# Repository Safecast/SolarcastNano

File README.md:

# Solarcast Nano

SCNano-1.0          Original Design files for Solarcast Nano 1.0 (PCB in Altium, Mechanical in Alibre)

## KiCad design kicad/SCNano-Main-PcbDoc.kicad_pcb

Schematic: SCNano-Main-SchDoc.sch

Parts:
ANT1: 3G Antenna
BAT1: KEYSTONE_1049
BOM1: Battery - 1of 2
BOM2: Battery - 2 of 2
C1: CAP POL RB13-25
CON1: SC_CON_GEIGIE_4PIN
IC1: SN74LV4052A
J1: (no value)
MOD1: LiPo Charger
MOD2, MOD2_2: FONA 3G
MOD3: Current Sensor
MOD4: 3-Axis
MOD5: GPS
MOD6: Nano V2
MOD7: DAPLink 1.5
MOD8: MicroUSB
OLED1: OLED 128x64
Q1, Q2, Q3, Q4: STU85N3LH5
SOLARPANEL1: VOLTAIC_SOLAR_PANEL_1W
SW1: SW-DPDT
VREG1: Regulator 3.3V
VREG2: Regulator Variable

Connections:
3V3: CON1.2 (RED(3V3)), IC1.16 (VCC), MOD2.4 (Vio), MOD2.5 (RST(Reset)), MOD3.1 (Vcc), MOD4.2 (3Vo), MOD5.8 (VIN), MOD6.2-1 (VDD(3.3V)), MOD7.2-1 (VDD/+3.3Vout), OLED1.1 (VCC), VREG1.1 (VOUT)
/BAT-BUS: MOD1.3 (B+), MOD3.5 (Vin-), VREG1.3 (VIN), VREG2.1 (VIN)
/BAT-POS: BAT1.1 (+), BAT1.3 (+), SW1.1
/BAT-SW: MOD3.6 (Vin+), SW1.2
/ENABLE-CELL: IC1.9 (B), MOD6.3-4 (P08), Q1.1 (G)
/ENABLE-GEIG: MOD6.3-1 (P03), Q3.1 (G)
/ENABLE-GPS: IC1.10 (A), MOD6.3-3 (P07), Q4.1 (G)
/ENABLE_TWI: MOD6.3-2 (P06), Q2.1 (G)
/FONA-BAT: MOD2.2 (Battery), VREG2.3 (VOUT)
/FONA-RX: IC1.2 (2Y2), MOD2.6 (RX)
/FONA-TX: IC1.15 (1Y2), MOD2.7 (TX)
/GEIGER0: CON1.4 (YEL(GEIGER0)), MOD6.1-4 (P04), MOD7.1-4 (NC[P04])
/GEIGER1: CON1.3 (WHT(GEIGER1)), MOD6.1-3 (P05), MOD7.1-3 (NC[P05])
/GND-CELL: MOD2.3 (GND), MOD2.11 (Key), Q1.2 (D), VREG2.2 (GND)
/GND-GEIG: CON1.1 (BLK(GND)), Q3.2 (D)
/GND-GPS: MOD5.7 (GND), Q4.2 (D)
/GND-TWI: MOD3.2 (Gnd), OLED1.2 (GND), Q2.2 (D)
/LIS-INT: MOD4.8 (INT), MOD6.3-5 (P21)
/MCU-RX: IC1.13 (1-COM), MOD6.2-4 (N2:RX/P30), MOD7.2-4 (DL:TXD[P30])
/MCU-SWCLK: MOD6.1-1 (DCLK), MOD7.1-1 (SWDCLK)
/MCU-SWDIO: MOD6.1-2 (DIO), MOD7.1-2 (SWDIO)
/MCU-TX: IC1.3 (2-COM), MOD6.2-3 (N2:TX/P29), MOD7.2-3 (DL:RXD[P29])
/NANO_VIN: MOD6.1-6 (VIN(USB5V)), MOD7.1-6 (VIN/USB5V)
/PANEL-POS: J1.1, MOD1.1 (DCIN+[TB1]), MOD8.5 (5V)
/TWI-SCL: MOD3.3 (Scl), MOD4.4 (SCL), MOD6.2-5 (N2:RTS/P02), MOD7.2-5 (DL:CTS[P31]), OLED1.3 (SCL)
/TWI-SDA: MOD3.4 (Sda), MOD4.5 (SDA), MOD6.2-2 (N2:CTS/P28), MOD7.2-2 (DL:RTS[P28]), OLED1.4 (SDA)
/UGPS-RX: IC1.5 (2Y1), MOD5.6 (RX)
/UGPS-TX: IC1.14 (1Y1), MOD5.5 (TX)
GND: BAT1.2 (-), BAT1.4 (-), C1.2, IC1.6 (INH), IC1.7 (GND), IC1.8 (GND), J1.2, MOD1.2 (DCIN-[TB1]), MOD1.4 (GND), MOD1.6 (C4-/GND), MOD1.8 (GND), MOD4.3 (GND), MOD6.1-5 (GND), MOD6.2-6 (GND), MOD7.1-5 (GND), MOD7.2-6 (GND), MOD8.1 (GND), Q1.3 (S), Q2.3 (S), Q3.3 (S), Q4.3 (S), VREG1.2 (GND)
unnamed: C1.1, MOD1.5 (C4+)

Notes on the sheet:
=sheetnumber
=organization
=address1
=address2
=address3
=address4
=sheettotal
=title
=documentnumber
=revision
=CurrentDate
=CurrentTime
=DocumentFullPathAndName
Title
Size:
Number:
Date:
File:
Revision:
Sheet
Time:
>>> Cable to Geiger Board
Note: USB A(F)/Micro-B(M) Retractable Cable
FET0
FET1
FET2
FET3
Note: Misc. Headers, Hardware
Note: Enclosure: Pelican 1040, modified with circular cutout and mylar film.
Power In
Charge Monitoring
OLED Display
3-Axis sensor
Microprocessor
Programming Interface
Connection to Geiger Board
TWI Bus
GPS
3G Data
3.3V Regulator (System Power)

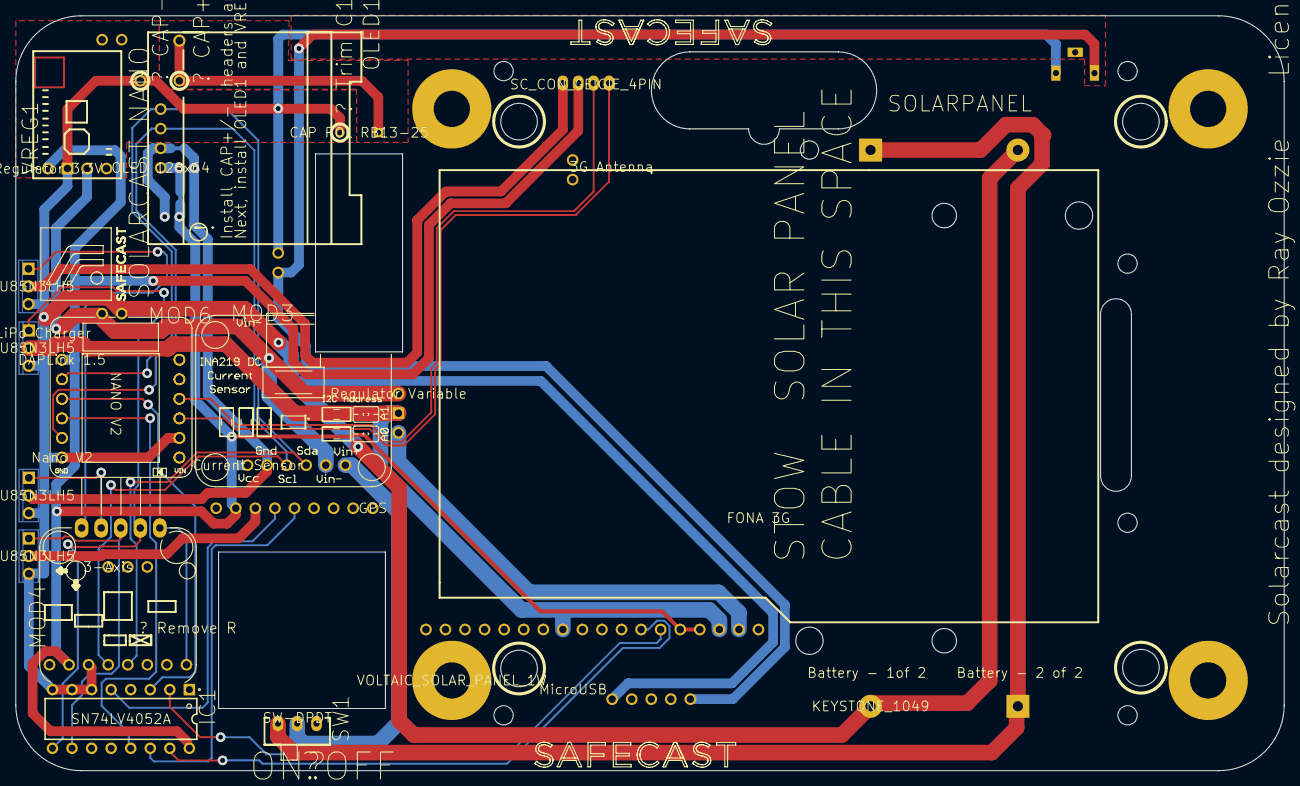
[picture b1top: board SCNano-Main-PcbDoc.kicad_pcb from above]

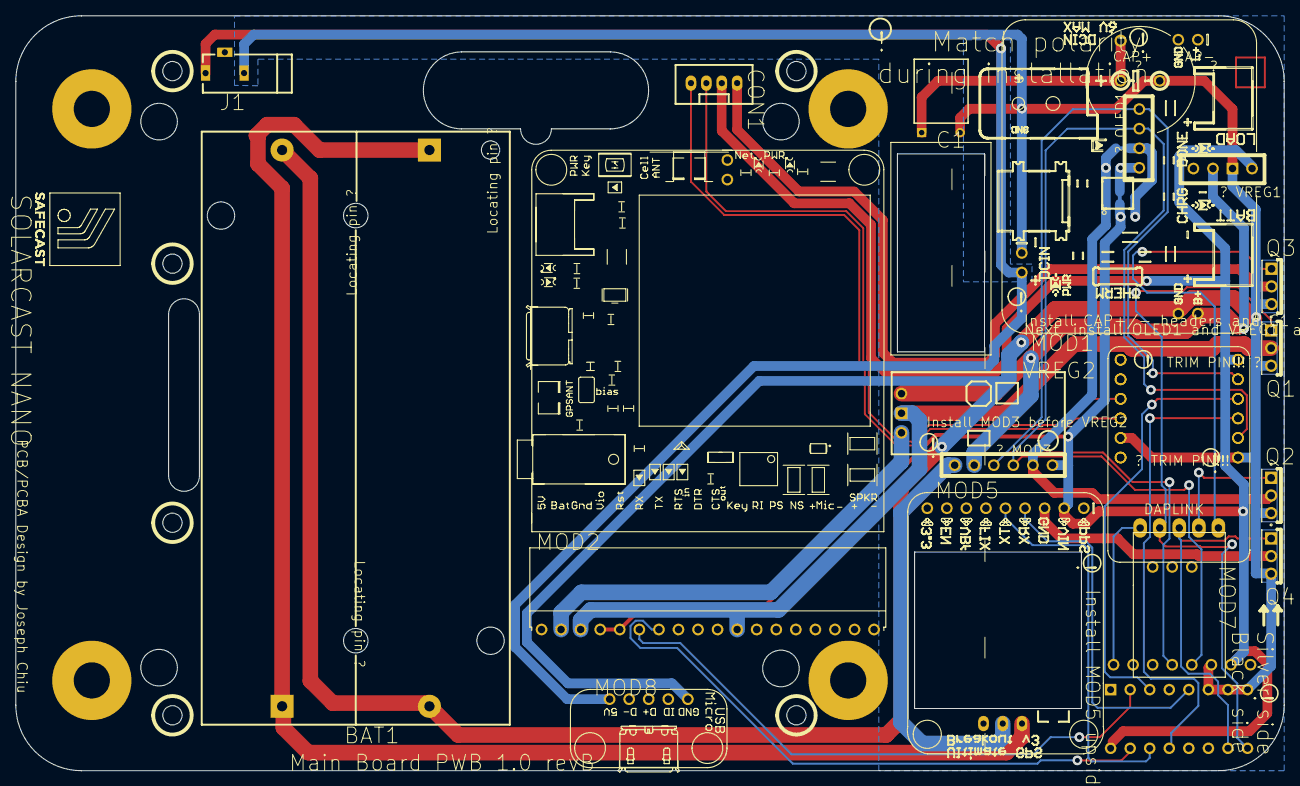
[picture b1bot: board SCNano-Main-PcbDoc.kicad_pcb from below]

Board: 2 copper layers, 164.7 x 98.0 mm, 25 parts (17 on the bottom side), 30 nets.

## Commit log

2017-12-16 Setting up for initial release
2017-12-16 Initial checkin
2017-12-16 Initial KiCAD conversion of PCB
2017-12-18 Work in progress - conversion to KiCAD. There are still known problems in the conversion.
2017-12-18 Remove alternate-mode symbols in RedBear Altium schematic symbols to prevent overlapped symbols in converted KiCAD schematic
2017-12-18 Some more fixes for symbol related issues
2017-12-18 Altium Class Name directives are unsupported in KiCAD. The conversion process placed the same ClassName directives as labels, which caused multiple nets to be treated as the same net. Changed those l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

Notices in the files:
kicad/SCNano-Main-PcbDoc.kicad_pcb:
Solarcast designed by Ray Ozzie Licensed CC BY-SA 3.0 safecast.org
